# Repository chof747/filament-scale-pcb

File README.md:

# Samla Filamentalist Electronics

## Idea

This is the electronics part of the filamentalist samla box which consists of:

### 1. The scale breakout for each Filamentalist station that contains:

- A header to read from a load cell
- An HX711 ADC controller and circutry to read the load cell
- A peripheral connector to connect to the led and the button on the outside of the box of the filamentalist station
- An IDC header to connect to the central mcu unit

### 2. An MCU Breakout

A board that bears the MCU and brain of the Filamentalist Box it has

- IDC receiving headers for each scale
- A header to connect to an SHT40X breakout for environmental control
- A 0.9" OLED
- A reset and a mod button to controll the oled

## Components

- Arduino Nano as the MCU
- 0.9" OLED
- 2x SMD Push Buttons
- 3 IDC headers
- 1 JST XH 2.54mm header (environmental sensor)

- HX711 ADC
- Screw terminal for Load cell connections
- IDC Header to MCU
- Peripheral JST xh 2.54mm for peripherals

## Revision History

**V1.0** - Send to production 26.07.2025
**Breakout Board V1.1** - separated clock lines for the three scales

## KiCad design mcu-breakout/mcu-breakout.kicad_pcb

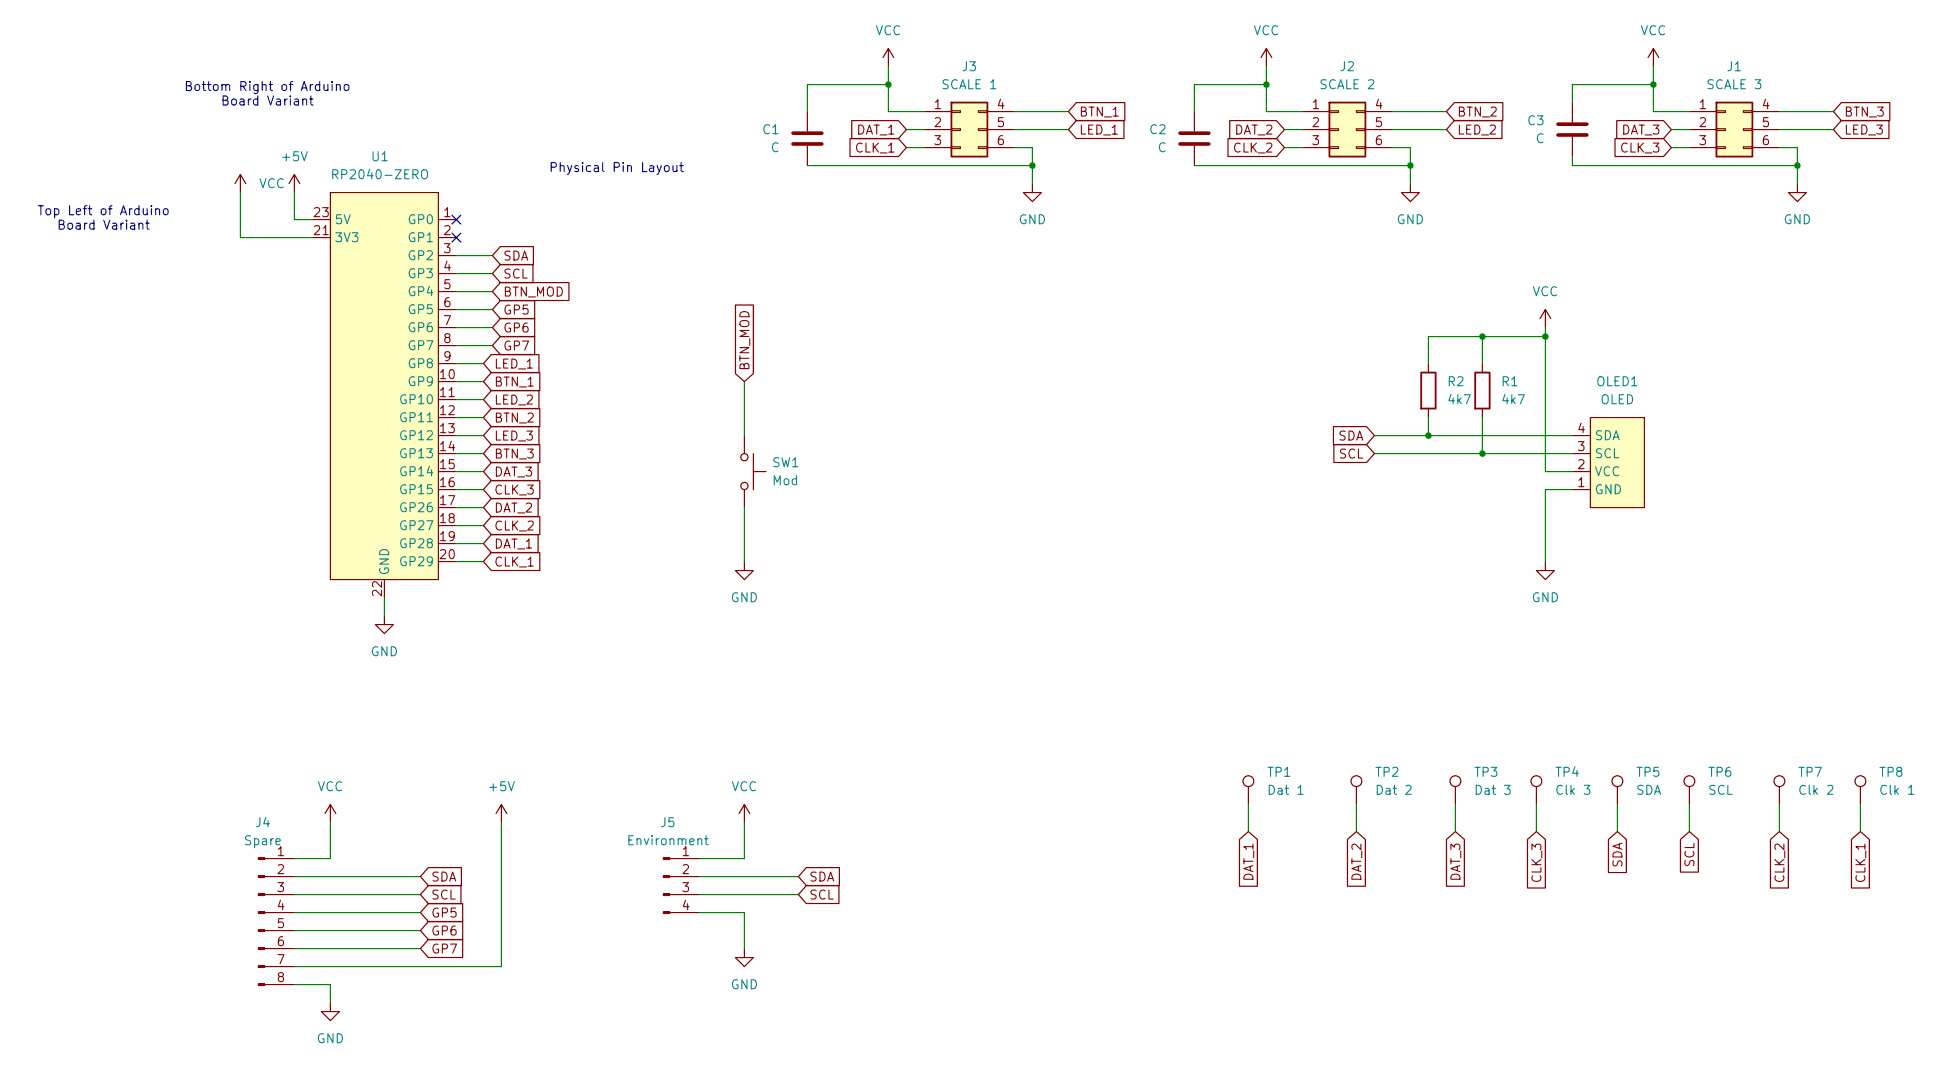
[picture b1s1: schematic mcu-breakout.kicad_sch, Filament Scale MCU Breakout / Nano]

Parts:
C1, C2, C3: C; C_0603_1608Metric_Pad1.08x0.95mm_HandSolder
J1: SCALE 3; HDR-TH_6P-P2.54-V-F-R2-C3-S2.54-4
J2: SCALE 2; HDR-TH_6P-P2.54-V-F-R2-C3-S2.54-4
J3: SCALE 1; HDR-TH_6P-P2.54-V-F-R2-C3-S2.54-4
J4: Spare; PinHeader_1x08_P2.54mm_Vertical
J5: Environment; JST_XH_B4B-XH-A_1x04_P2.54mm_Vertical
OLED1: OLED; OLED-TH_L38.0-W12.0_HS91L02W2C01; LCSC Part C5248081
R1, R2: 4k7; R_0603_1608Metric_Pad0.98x0.95mm_HandSolder
SW1: Mod; KEY-SMD_L3.9-W3.0-LS5.0-EH
TP1: Dat 1; TestPoint_Pad_D2.0mm
TP2: Dat 2; TestPoint_Pad_D2.0mm
TP3: Dat 3; TestPoint_Pad_D2.0mm
TP4: Clk 3; TestPoint_Pad_D2.0mm
TP5: SDA; TestPoint_Pad_D2.0mm
TP6: SCL; TestPoint_Pad_D2.0mm
TP7: Clk 2; TestPoint_Pad_D2.0mm
TP8: Clk 1; TestPoint_Pad_D2.0mm
U1: RP2040-ZERO; RP2040-ZERO-THP; LCSC Part C5350143

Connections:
+5V: J4.7, U1.23 (5V)
BTN_1: J3.4, U1.10 (GP9)
BTN_2: J2.4, U1.12 (GP11)
BTN_3: J1.4, U1.14 (GP13)
BTN_MOD: SW1.1, U1.5 (GP4)
CLK_1: J3.3, TP8.1, U1.20 (GP29)
CLK_2: J2.3, TP7.1, U1.18 (GP27)
CLK_3: J1.3, TP4.1, U1.16 (GP15)
DAT_1: J3.2, TP1.1, U1.19 (GP28)
DAT_2: J2.2, TP2.1, U1.17 (GP26)
DAT_3: J1.2, TP3.1, U1.15 (GP14)
GND: C1.2, C2.2, C3.2, J1.6, J2.6, J3.6, J4.8, J5.4, OLED1.1 (GND), SW1.2, U1.22 (GND)
GP5: J4.4, U1.6 (GP5)
GP6: J4.5, U1.7 (GP6)
GP7: J4.6, U1.8 (GP7)
LED_1: J3.5, U1.9 (GP8)
LED_2: J2.5, U1.11 (GP10)
LED_3: J1.5, U1.13 (GP12)
SCL: J4.3, J5.3, OLED1.3 (SCL), R1.2, TP6.1, U1.4 (GP3)
SDA: J4.2, J5.2, OLED1.4 (SDA), R2.2, TP5.1, U1.3 (GP2)
VCC: C1.1, C2.1, C3.1, J1.1, J2.1, J3.1, J4.1, J5.1, OLED1.2 (VCC), R1.1, R2.1, U1.21 (3V3)

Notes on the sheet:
Bottom Right of Arduino Board Variant
Top Left of Arduino Board Variant
Physical Pin Layout

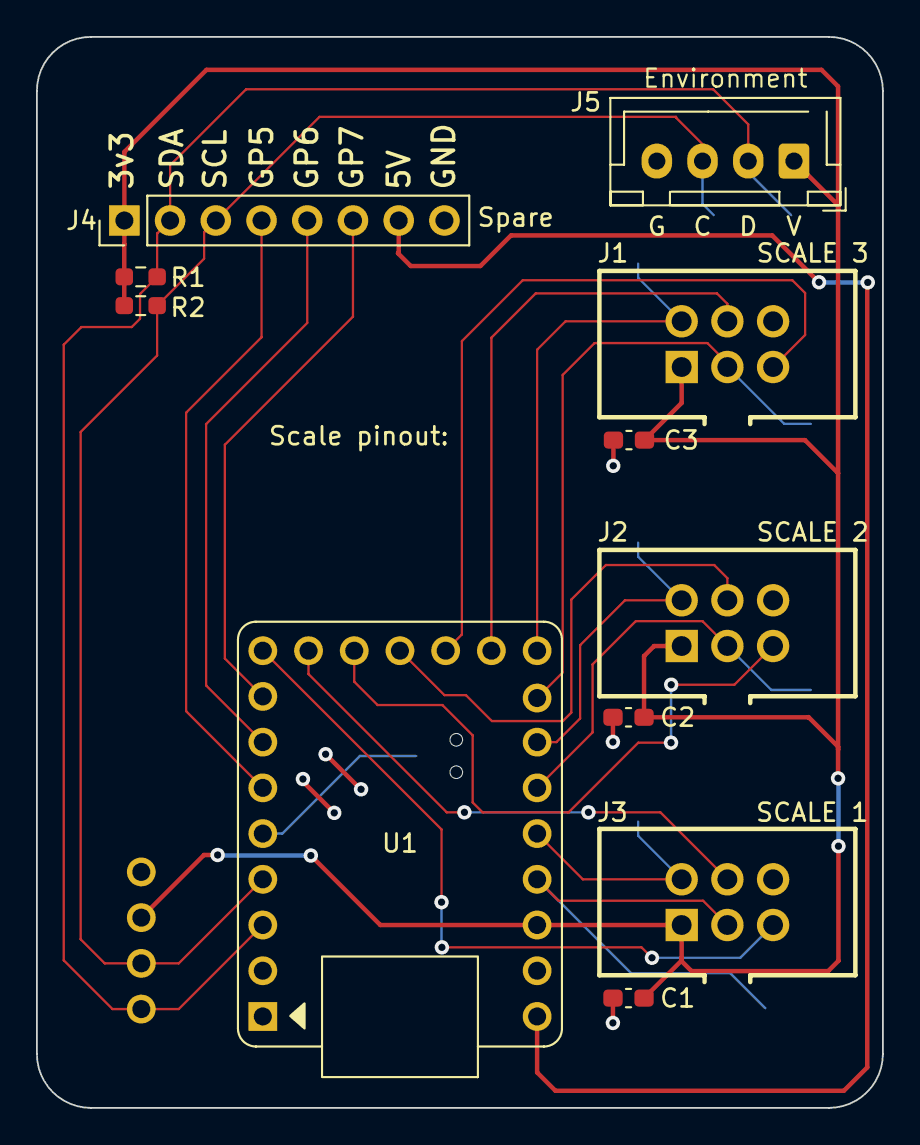
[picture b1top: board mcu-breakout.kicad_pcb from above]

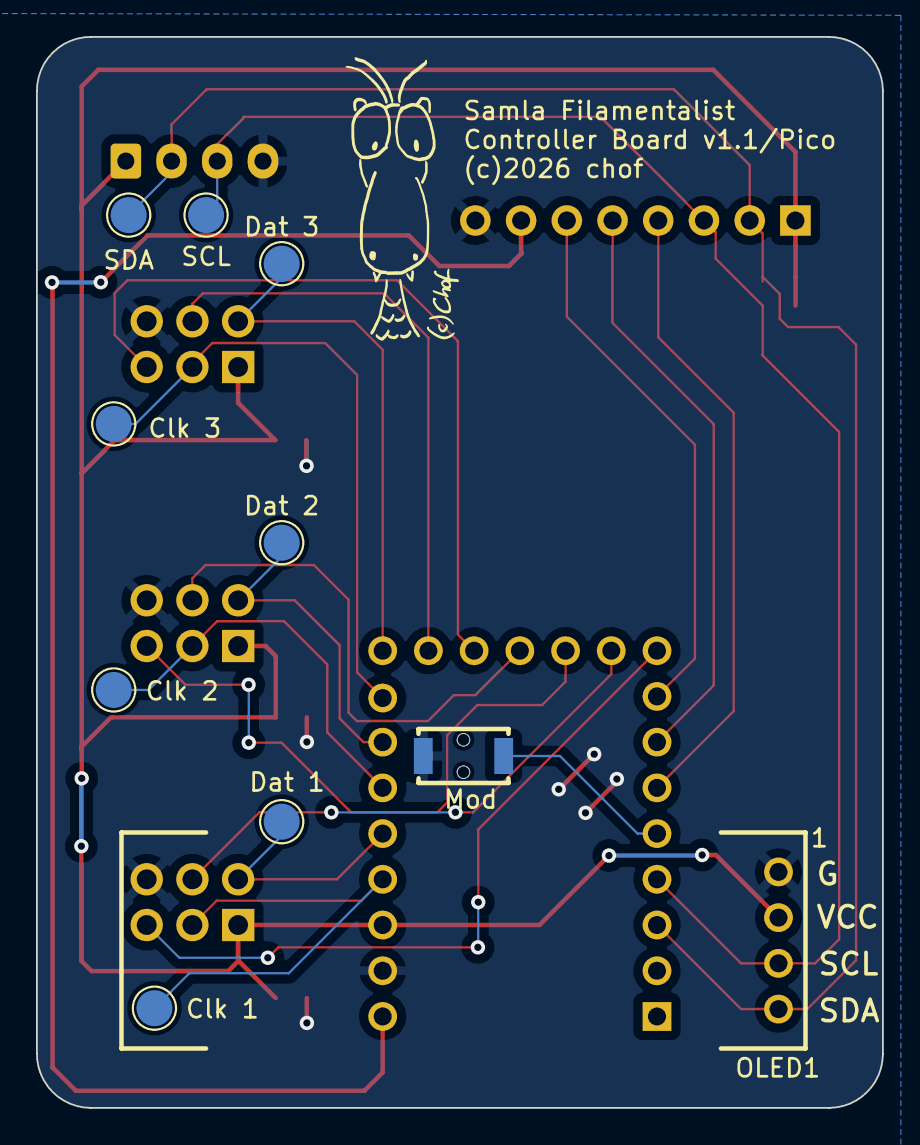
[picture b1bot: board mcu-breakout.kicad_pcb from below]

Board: 2 copper layers, 47.0 x 59.5 mm, 21 parts (10 on the bottom side), 21 nets.

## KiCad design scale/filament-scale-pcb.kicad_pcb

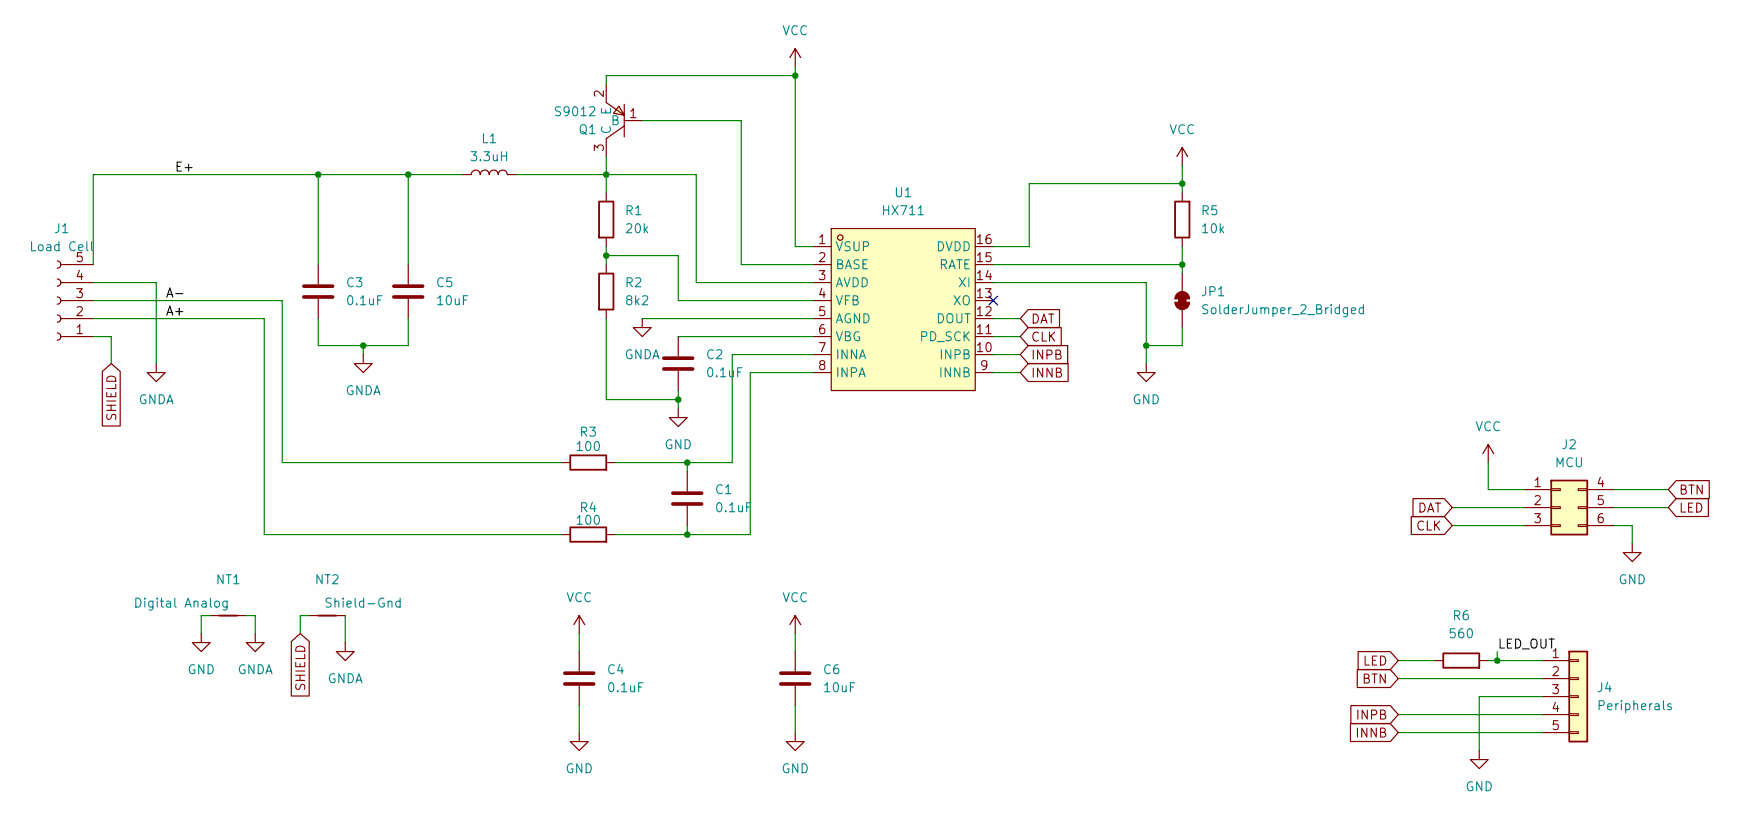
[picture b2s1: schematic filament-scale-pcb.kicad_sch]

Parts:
C1, C2, C3, C4: 0.1uF; C_0603_1608Metric_Pad1.08x0.95mm_HandSolder
C5, C6: 10uF; C_0603_1608Metric_Pad1.08x0.95mm_HandSolder
J1: Load Cell; CONN-TH_5P-P2.54_KF128-2.54-5P
J2: MCU; HDR-TH_6P-P2.54-V-F-R2-C3-S2.54-4
J4: Peripherals; JST_XH_B5B-XH-A_1x05_P2.54mm_Vertical
JP1: SolderJumper_2_Bridged; SolderJumper-2_P1.3mm_Bridged_RoundedPad1.0x1.5mm
L1: 3.3uH; L_0603_1608Metric_Pad1.05x0.95mm_HandSolder
NT1: Digital Analog; NetTie-2_SMD_Pad0.5mm
NT2: Shield-Gnd; NetTie-2_SMD_Pad0.5mm
Q1: S9012; SOT-23-3_L2.9-W1.3-P1.90-LS2.4-BR; LCSC Part C545570
R1: 20k; R_0603_1608Metric_Pad0.98x0.95mm_HandSolder
R2: 8k2; R_0603_1608Metric_Pad0.98x0.95mm_HandSolder
R3, R4: 100; R_0603_1608Metric_Pad0.98x0.95mm_HandSolder
R5: 10k; R_0603_1608Metric_Pad0.98x0.95mm_HandSolder
R6: 560; R_0603_1608Metric_Pad0.98x0.95mm_HandSolder
U1: HX711; SOP-16_L10.0-W3.9-P1.27-LS6.0-BL; LCSC Part C6705483

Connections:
/A+: J1.2, R4.1
/A-: J1.3, R3.1
/E+: C3.1, C5.1, J1.5, L1.1
/LED_OUT: J4.1, R6.2
BTN: J2.4, J4.2
CLK: J2.3, U1.11 (PD_SCK)
DAT: J2.2, U1.12 (DOUT)
GND: C2.1, C4.2, C6.2, J2.6, J4.3, JP1.1 (A), NT1.2, R2.2, U1.14 (XI)
GNDA: C3.2, C5.2, J1.4, NT1.1, NT2.1, U1.5 (AGND)
INNB: J4.5, U1.9 (INNB)
INPB: J4.4, U1.10 (INPB)
LED: J2.5, R6.1
unnamed: JP1.2 (B), R5.1, U1.15 (RATE)
unnamed: Q1.1 (B), U1.2 (BASE)
unnamed: L1.2, Q1.3 (C), R1.1, U1.3 (AVDD)
unnamed: C1.1, R3.2, U1.7 (INNA)
unnamed: C1.2, R4.2, U1.8 (INPA)
unnamed: C2.2, U1.6 (VBG)
unnamed: R1.2, R2.1, U1.4 (VFB)
SHIELD: J1.1, NT2.2
VCC: C4.1, C6.1, J2.1, Q1.2 (E), R5.2, U1.1 (VSUP), U1.16 (DVDD)

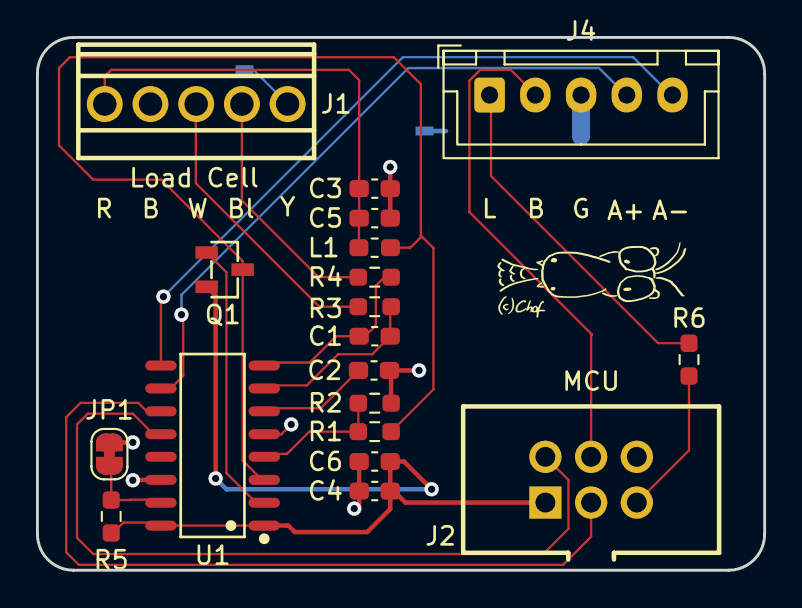
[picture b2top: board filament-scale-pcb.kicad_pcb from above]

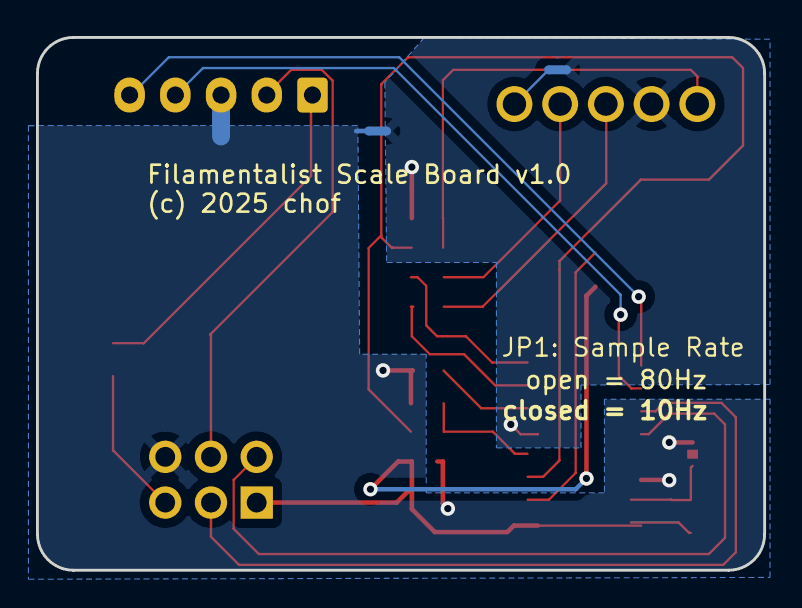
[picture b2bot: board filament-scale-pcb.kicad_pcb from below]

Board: 2 copper layers, 40.4 x 29.6 mm, 21 parts (2 on the bottom side), 21 nets.

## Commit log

2025-07-21 V1.0 of Filamentalist Samla electronics
2025-07-26 initial version for production
2026-01-31 Changed to separeted clock lines for the different scales
2026-03-10 changes during build
2026-03-13 changed to pico as a mcu
2026-03-13 added schema print out and table with physical pin numbering to arduino version
2026-03-13 V1.1 Pico version - last changes during upload

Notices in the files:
mcu-breakout/mcu-breakout.kicad_pcb:
(c)2026 chof
scale/filament-scale-pcb.kicad_pcb:
(c) 2025 chof
